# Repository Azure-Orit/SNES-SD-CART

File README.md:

SD card reader for a modified SNES cartridge slot conected to a Raspberry Pi
Not tested yet

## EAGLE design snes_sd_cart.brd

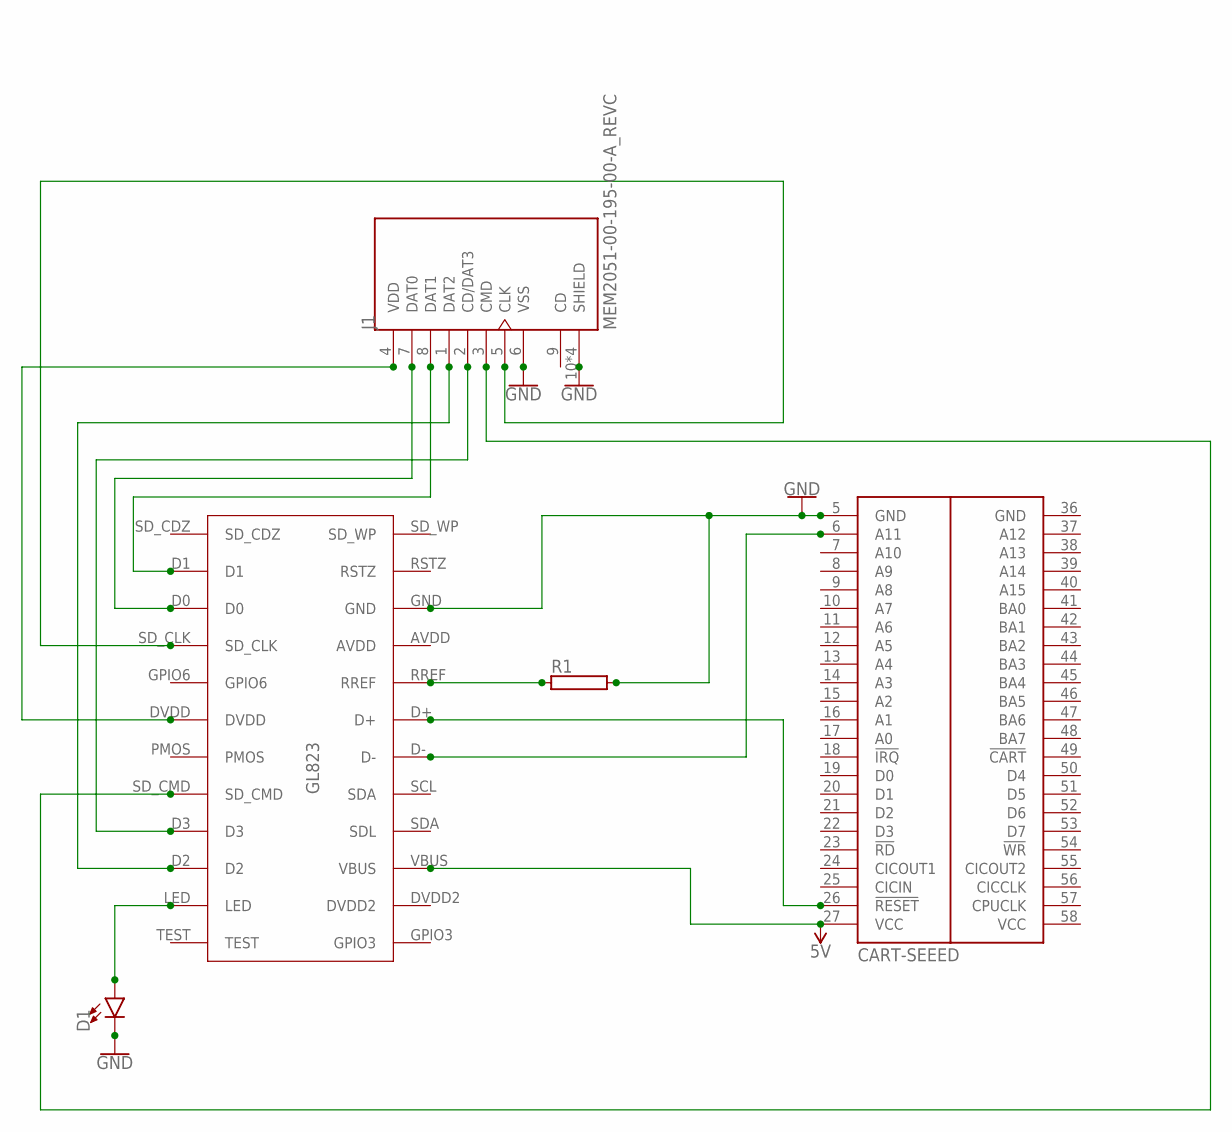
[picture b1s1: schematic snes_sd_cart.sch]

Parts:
D1: LED-3MM-NO_SILK; LED_3MM-NS
J1: MEM2051-00-195-00-A_REVC; GCT_MEM2051-00-195-00-A_REVC
R1: RAC01; AC01
U$1: CART-SEEED; CART-50MM
U$2: GL823

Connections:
5V: U$1.27 (VCC), U$2.VBUS
GND: D1.K (C), J1.6 (VSS), J1.10 (SHIELD), J1.11 (SHIELD), J1.12 (SHIELD), J1.13 (SHIELD), R1.2, U$1.5 (GND), U$1.36 (GND), U$2.GND
unnamed: J1.7 (DAT0), U$2.D0
unnamed: J1.8 (DAT1), U$2.D1
unnamed: J1.1 (DAT2), U$2.D2
unnamed: J1.2 (CD/DAT3), U$2.D3
unnamed: J1.3 (CMD), U$2.SD_CMD
unnamed: J1.5 (CLK), U$2.SD_CLK
unnamed: R1.1, U$2.RREF
unnamed: J1.4 (VDD), U$2.DVDD
unnamed: U$1.26 (!RESET), U$2.D+
unnamed: U$1.6 (A11), U$2.D-
unnamed: D1.A, U$2.LED
VCC: U$1.58 (VCC)

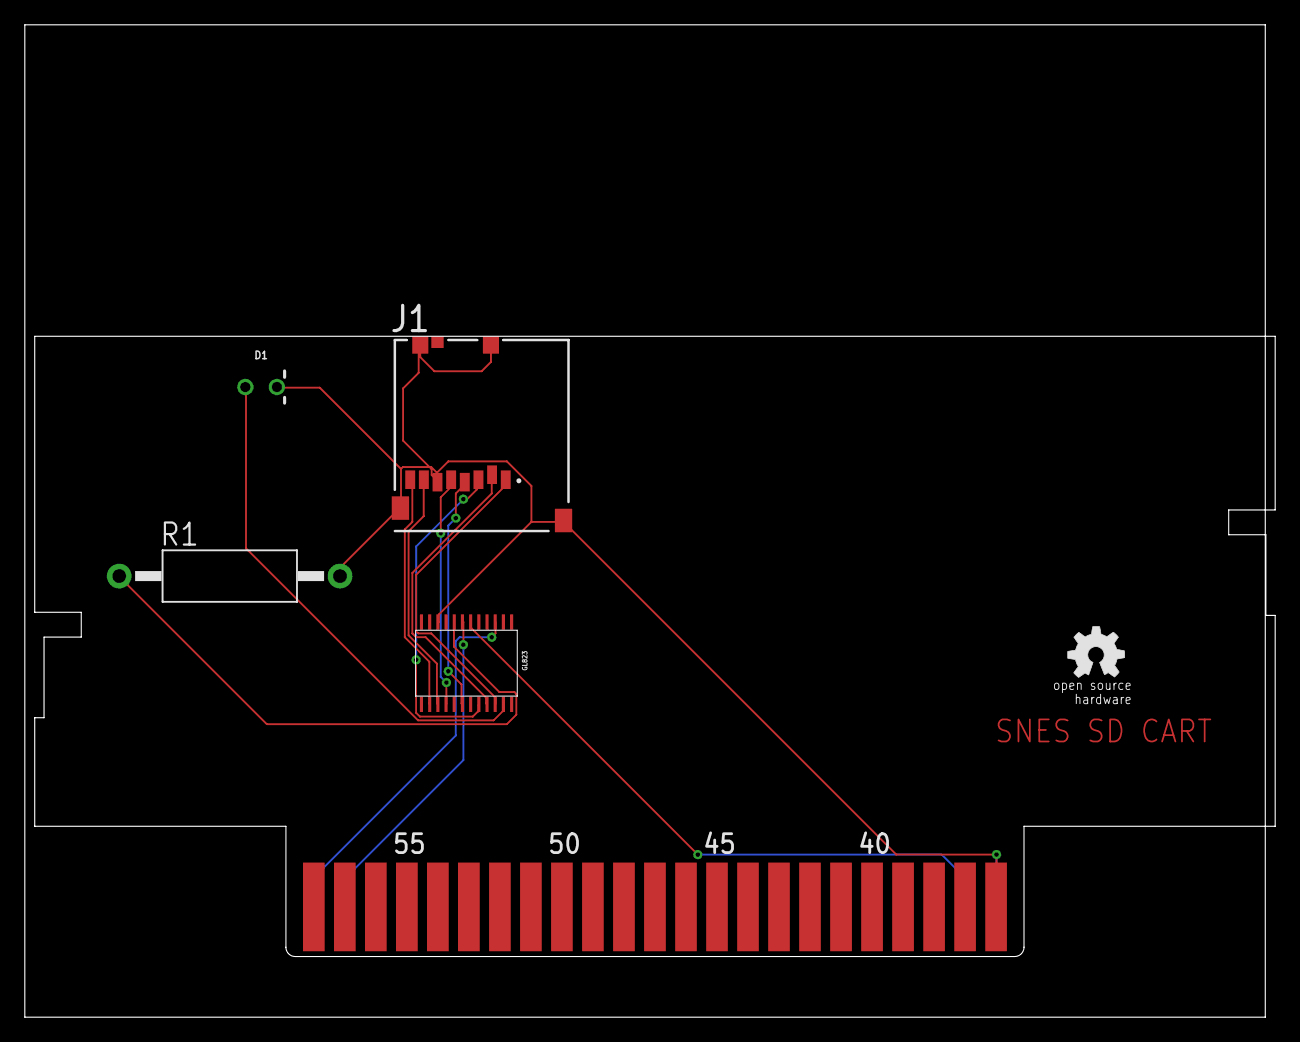
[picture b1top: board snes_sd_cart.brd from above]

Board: 2 copper layers, 100.8 x 80.0 mm, 6 parts (0 on the bottom side), 13 nets.

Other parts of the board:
E$1: OSHW_5MM

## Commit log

2021-03-01 Initial Upload

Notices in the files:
parts and their libraries:
SparkFun-LED: Licensing: Creative Commons ShareAlike 4.0 International - https://creativecommons.org/licenses/by-sa/4.0
